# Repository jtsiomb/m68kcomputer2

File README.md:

Homebrew 32bit computer
=======================

About
-----
Following after my minimal 16bit 68010 computer design
(https://github.com/jtsiomb/m68kcomputer) this is an attempt to make a much
more advanced 32bit computer, based on the Motorola 68030 CPU.

The main objective of this project is to make a stand-alone computer, capable of
running a custom UNIX system with virtual memory. The 68030 processor was chosen
because it has an on-chip MMU.

The plan is to include the following on the main board:
 - Analog video output
 - PS/2 keyboard controller
 - ATA hard drive interface for fixed storage
 - SD card for removable storage
 - 68881 floating point co-processor
 - Dual RS232 serial port
 - Battery-backed RTC

Directory structure:
 - `hw` - hardware: kicad files and pdf schematics.

Design Progress
---------------

### Main board ###
 - [X] Schematic: almost completed, minor tweaks, video left for an expansion
 - [ ] PCB layout: not started
 - [ ] Firmware: not started
 - [ ] Boot ROM monitor: not started
 - [ ] Operating system: not started

### Video expansion card ###
 - [ ] Schematic
 - [ ] PCB layout
 - [ ] OS support

### Audio expansion card ###
 - [ ] Schematic
 - [ ] PCB layout
 - [ ] OS support

License
-------
Copyright (C) 2022 John Tsiombikas <nuclear@member.fsf.org>

You are free to use, reproduce, modify, and redistribute any part of this
project, provided you make any derivative work you release, freely available
under the same terms.

Both hardware designs, and software parts of this project, are released under
the terms of the GNU General Public License v3, or at your option any later
version published by the Free Software Foundation. See `LICENSE` for details.

To comply with the license, when releasing derivative hardware designs, you
must provide the full EDA project files, GAL equation files, and of course
firmware/software source code. Releasing only images of schematics, gerbers,
JED files, and firmware binaries is *not* sufficient for compliance.

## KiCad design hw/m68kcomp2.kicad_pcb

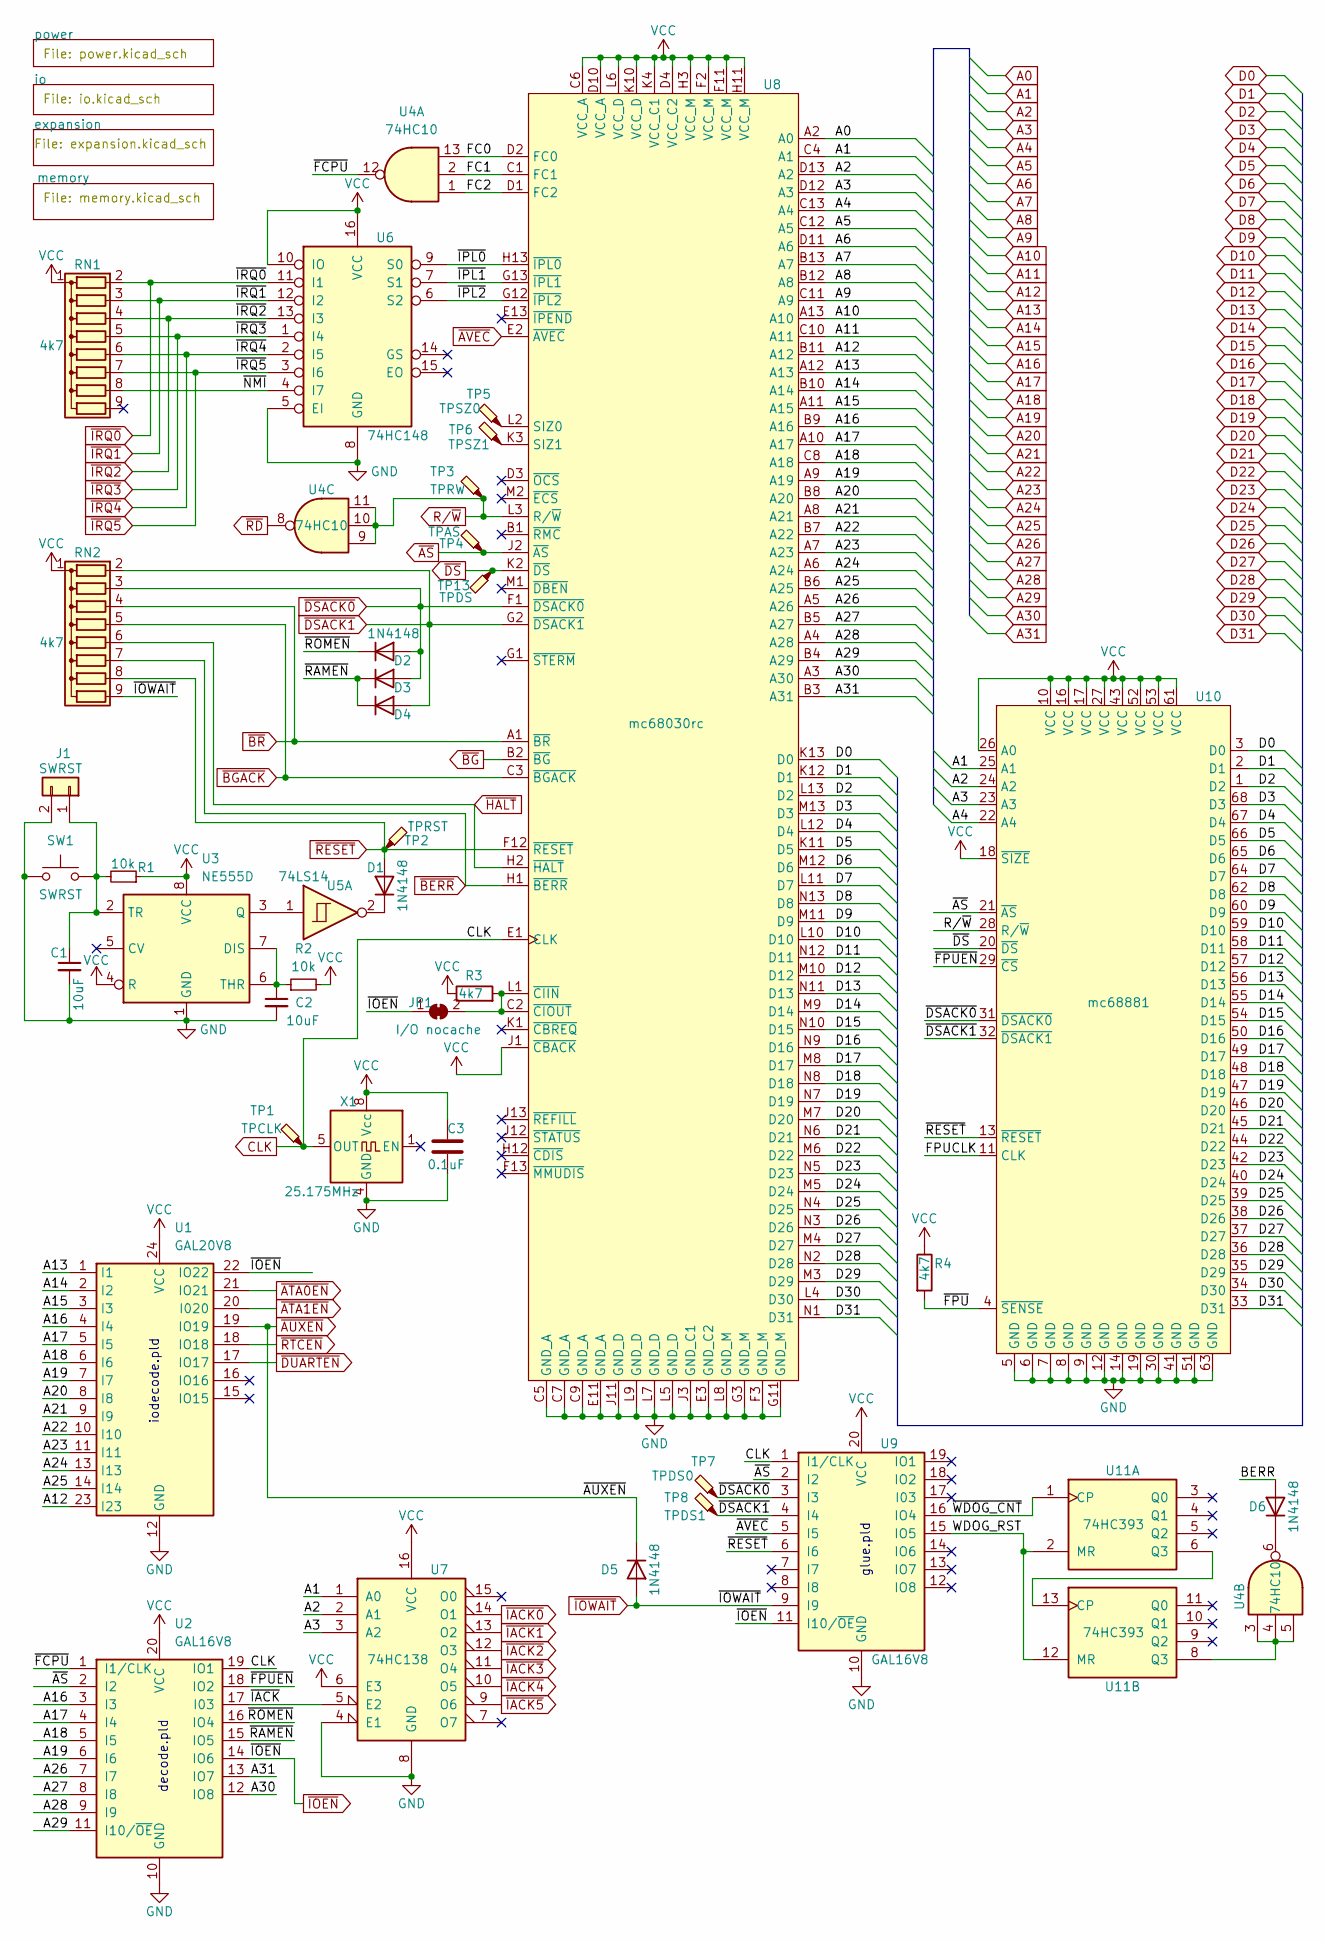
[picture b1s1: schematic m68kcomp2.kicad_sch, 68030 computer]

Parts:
C1, C2: 10uF; C_0805_2012Metric_Pad1.18x1.45mm_HandSolder
C3: 0.1uF; C_0805_2012Metric_Pad1.18x1.45mm_HandSolder
D1, D2, D3, D4, D5, D6: 1N4148; D_DO-35_SOD27_P7.62mm_Horizontal
J1: SWRST; PinHeader_1x02_P2.54mm_Vertical
JP1: I/O nocache; SolderJumper-2_P1.3mm_Bridged_RoundedPad1.0x1.5mm
R1, R2: 10k; R_0805_2012Metric_Pad1.20x1.40mm_HandSolder
R3, R4: 4k7; R_0805_2012Metric_Pad1.20x1.40mm_HandSolder
RN1, RN2: 4k7; R_Array_SIP9
SW1: SWRST; SW_SPST_EVPBF
TP1: TPCLK; TestPoint_Pad_D1.5mm
TP2: TPRST; TestPoint_Pad_D1.5mm
TP3: TPRW; TestPoint_Pad_D1.5mm
TP4: TPAS; TestPoint_Pad_D1.5mm
TP5: TPSZ0; TestPoint_Pad_D1.5mm
TP6: TPSZ1; TestPoint_Pad_D1.5mm
TP7: TPDS0; TestPoint_Pad_D1.5mm
TP8: TPDS1; TestPoint_Pad_D1.5mm
TP13: TPDS; TestPoint_Pad_D1.5mm
U1: GAL20V8; DIP-24_W7.62mm_Socket
U2, U9: GAL16V8; DIP-20_W7.62mm_Socket
U3: NE555D; SOIC-8_3.9x4.9mm_P1.27mm
U4: 74HC10; SO-14_3.9x8.65mm_P1.27mm
U5: 74LS14; SO-14_3.9x8.65mm_P1.27mm
U6: 74HC148; SO-16_3.9x9.9mm_P1.27mm
U7: 74HC138; SO-16_3.9x9.9mm_P1.27mm
U8: mc68030rc
U10: mc68881; PLCC-68_THT-Socket
U11: 74HC393; SO-14_3.9x8.65mm_P1.27mm
X1: 25.175MHz; Oscillator_DIP-8

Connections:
/BERR: D6.2 (A)
/FC0: U4.13, U8.D2 (FC0)
/FC1: U4.2, U8.C1 (FC1)
/FC2: U4.1, U8.D1 (FC2)
/FPUCLK: U10.11 (CLK)
/WDOG_RST: U9.15 (IO5), U11.2 (MR), U11.12 (MR)
/~FCPU: U2.1 (I1/CLK), U4.12
/~FPUEN: U2.18 (IO2), U10.29 (~CS)
/~FPU: R4.2, U10.4 (~SENSE)
/~IACK: U2.17 (I03), U7.5 (E2)
/~IPL0: U6.9 (S0), U8.H13 (~IPL0)
/~IPL1: U6.7 (S1), U8.G13 (~IPL1)
/~IPL2: U6.6 (S2), U8.G12 (~IPL2)
/~NMI: RN1.8 (R7), U6.4 (I7)
/~RAMEN: D3.1 (K), D4.1 (K), U2.15 (IO5)
/~ROMEN: D2.1 (K), U2.16 (IO4)
/~WDOG_CNT: U9.16 (IO4), U11.1 (CP)
A0: U8.A2 (A0); also elsewhere on the board
A1: U7.1 (A0), U8.C4 (A1), U10.25 (A1); also elsewhere on the board
A2: U7.2 (A1), U8.D13 (A2), U10.24 (A2); also elsewhere on the board
A3: U7.3 (A2), U8.D12 (A3), U10.23 (A3); also elsewhere on the board
A4: U8.C13 (A4), U10.22 (A4); also elsewhere on the board
A5: U8.C12 (A5); also elsewhere on the board
A6: U8.D11 (A6); also elsewhere on the board
A7: U8.B13 (A7); also elsewhere on the board
A8: U8.B12 (A8); also elsewhere on the board
A9: U8.C11 (A9); also elsewhere on the board
A10: U8.A13 (A10); also elsewhere on the board
A11: U8.C10 (A11); also elsewhere on the board
A12: U1.23 (I23), U8.B11 (A12); also elsewhere on the board
A13: U1.1 (I1), U8.A12 (A13); also elsewhere on the board
A14: U1.2 (I2), U8.B10 (A14); also elsewhere on the board
A15: U1.3 (I3), U8.A11 (A15); also elsewhere on the board
A16: U1.4 (I4), U2.3 (I3), U8.B9 (A16); also elsewhere on the board
A17: U1.5 (I5), U2.4 (I4), U8.A10 (A17); also elsewhere on the board
A18: U1.6 (I6), U2.5 (I5), U8.C8 (A18); also elsewhere on the board
A19: U1.7 (I7), U2.6 (I6), U8.A9 (A19); also elsewhere on the board
A20: U1.8 (I8), U8.B8 (A20); also elsewhere on the board
A21: U1.9 (I9), U8.A8 (A21); also elsewhere on the board
A22: U1.10 (I10), U8.B7 (A22); also elsewhere on the board
A23: U1.11 (I11), U8.A7 (A23); also elsewhere on the board
A24: U1.13 (I13), U8.A6 (A24); also elsewhere on the board
A25: U1.14 (I14), U8.B6 (A25); also elsewhere on the board
A26: U2.7 (I7), U8.A5 (A26); also elsewhere on the board
A27: U2.8 (I8), U8.B5 (A27); also elsewhere on the board
A28: U2.9 (I9), U8.A4 (A28); also elsewhere on the board
A29: U2.11 (I10/~OE), U8.B4 (A29); also elsewhere on the board
A30: U2.12 (IO8), U8.A3 (A30); also elsewhere on the board
A31: U2.13 (IO7), U8.B3 (A31); also elsewhere on the board
CLK: TP1.1, U2.19 (IO1), U8.E1 (CLK), U9.1 (I1/CLK), X1.5 (OUT); also elsewhere on the board
D0: U8.K13 (D0), U10.3 (D0); also elsewhere on the board
D1: U8.K12 (D1), U10.2 (D1); also elsewhere on the board
D2: U8.L13 (D2), U10.1 (D2); also elsewhere on the board
D3: U8.M13 (D3), U10.68 (D3); also elsewhere on the board
D4: U8.L12 (D4), U10.67 (D4); also elsewhere on the board
D5: U8.K11 (D5), U10.66 (D5); also elsewhere on the board
D6: U8.M12 (D6), U10.65 (D6); also elsewhere on the board
D7: U8.L11 (D7), U10.64 (D7); also elsewhere on the board
D8: U8.N13 (D8), U10.62 (D8); also elsewhere on the board
D9: U8.M11 (D9), U10.60 (D9); also elsewhere on the board
D10: U8.L10 (D10), U10.59 (D10); also elsewhere on the board
D11: U8.N12 (D11), U10.58 (D11); also elsewhere on the board
D12: U8.M10 (D12), U10.57 (D12); also elsewhere on the board
D13: U8.N11 (D13), U10.56 (D13); also elsewhere on the board
D14: U8.M9 (D14), U10.55 (D14); also elsewhere on the board
D15: U8.N10 (D15), U10.54 (D15); also elsewhere on the board
D16: U8.N9 (D16), U10.50 (D16); also elsewhere on the board
D17: U8.M8 (D17), U10.49 (D17); also elsewhere on the board
D18: U8.N8 (D18), U10.48 (D18); also elsewhere on the board
D19: U8.N7 (D19), U10.47 (D19); also elsewhere on the board
D20: U8.M7 (D20), U10.46 (D20); also elsewhere on the board
D21: U8.N6 (D21), U10.45 (D21); also elsewhere on the board
D22: U8.M6 (D22), U10.44 (D22); also elsewhere on the board
D23: U8.N5 (D23), U10.42 (D23); also elsewhere on the board
D24: U8.M5 (D24), U10.40 (D24); also elsewhere on the board
D25: U8.N4 (D25), U10.39 (D25); also elsewhere on the board
D26: U8.N3 (D26), U10.38 (D26); also elsewhere on the board
D27: U8.M4 (D27), U10.37 (D27); also elsewhere on the board
D28: U8.N2 (D28), U10.36 (D28); also elsewhere on the board
D29: U8.M3 (D29), U10.35 (D29); also elsewhere on the board
D30: U8.L4 (D30), U10.34 (D30); also elsewhere on the board
D31: U8.N1 (D31), U10.33 (D31); also elsewhere on the board
GND: C1.2, C2.2, C3.2, J1.2, SW1.1, U1.12 (GND), U2.10 (GND), U3.1 (GND), U6.5 (EI), U6.8 (GND), U7.4 (E1), U7.8 (GND), U8.C5 (GND_A), U8.C7 (GND_A), U8.C9 (GND_A), U8.E3 (GND_C2), U8.E11 (GND_A), U8.F3 (GND_M), U8.G3 (GND_M), U8.G11 (GND_M), U8.J3 (GND_C1), U8.J11 (GND_D), U8.L5 (GND_D), U8.L7 (GND_D), U8.L8 (GND_M), U8.L9 (GND_D), U9.10 (GND), U10.5 (GND), U10.6 (GND), U10.7 (GND), U10.8 (GND), U10.9 (GND), U10.12 (GND), U10.14 (GND), U10.19 (GND), U10.30 (GND), U10.41 (GND), U10.51 (GND), U10.63 (GND), X1.4 (GND); also elsewhere on the board
unnamed: C1.1, J1.1, R1.2, SW1.2, U3.2 (TR)
unnamed: C2.1, R2.1, U3.6 (THR), U3.7 (DIS)
unnamed: D1.1 (K), U5.2
unnamed: D6.1 (K), U4.6
unnamed: JP1.2 (B), R3.2, U8.C2 (~CIOUT), U8.L1 (~CIIN)
unnamed: TP5.1, U8.L2 (SIZ0)
unnamed: TP6.1, U8.K3 (SIZ1)
unnamed: U3.3 (Q), U5.1
unnamed: U4.3, U4.4, U4.5, U11.8 (Q3)
unnamed: U11.6 (Q3), U11.13 (CP)
R/~W: TP3.1, U4.9, U4.10, U4.11, U8.L3 (R/~W), U10.28 (R/~W); also elsewhere on the board
VCC: C3.1, R1.1, R2.2, R3.1, R4.1, RN1.1 (common), RN2.1 (common), U1.24 (VCC), U2.20 (VCC), U3.4 (R), U3.8 (VCC), U6.10 (IO), U6.16 (VCC), U7.6 (E3), U7.16 (VCC), U8.C6 (VCC_A), U8.D4 (VCC_C2), U8.D10 (VCC_A), U8.F2 (VCC_M), U8.F11 (VCC_M), U8.H3 (VCC_M), U8.H11 (VCC_M), U8.J1 (~CBACK), U8.K4 (VCC_C1), U8.K10 (VCC_D), U8.L6 (VCC_D), U9.20 (VCC), U10.10 (VCC), U10.16 (VCC), U10.17 (VCC), U10.18 (~SIZE), U10.26 (A0), U10.27 (VCC), U10.43 (VCC), U10.52 (VCC), U10.53 (VCC), U10.61 (VCC), X1.8 (Vcc); also elsewhere on the board
~AS: TP4.1, U2.2 (I2), U8.J2 (~AS), U9.2 (I2), U10.21 (~AS); also elsewhere on the board
~ATA0EN: U1.21 (IO21); also elsewhere on the board
~ATA1EN: U1.20 (I020); also elsewhere on the board
~AUXEN: D5.1 (K), U1.19 (IO19); also elsewhere on the board
~AVEC: U8.E2 (~AVEC), U9.5 (I5); also elsewhere on the board
~BERR: RN2.7 (R6), U8.H1 (~BERR); also elsewhere on the board
~BGACK: RN2.5 (R4), U8.C3 (~BGACK); also elsewhere on the board
~BG: U8.B2 (~BG); also elsewhere on the board
~BR: RN2.4 (R3), U8.A1 (~BR); also elsewhere on the board
~DSACK0: D2.2 (A), D3.2 (A), RN2.3 (R2), TP7.1, U8.F1 (~DSACK0), U9.3 (I3), U10.31 (~DSACK0); also elsewhere on the board
~DSACK1: D4.2 (A), RN2.2 (R1), TP8.1, U8.G2 (~DSACK1), U9.4 (I4), U10.32 (~DSACK1); also elsewhere on the board
~DS: TP13.1, U8.K2 (~DS), U10.20 (~DS); also elsewhere on the board
~DUARTEN: U1.17 (IO17); also elsewhere on the board
~HALT: RN2.6 (R5), U8.H2 (~HALT); also elsewhere on the board
~IACK0: U7.14 (O1); also elsewhere on the board
~IACK1: U7.13 (O2); also elsewhere on the board
~IACK2: U7.12 (O3); also elsewhere on the board
~IACK3: U7.11 (O4); also elsewhere on the board
~IACK4: U7.10 (O5); also elsewhere on the board
~IACK5: U7.9 (O6); also elsewhere on the board
~IOEN: JP1.1 (A), U1.22 (IO22), U2.14 (IO6), U9.11 (I10/~OE); also elsewhere on the board
~IOWAIT: D5.2 (A), RN2.9 (R8), U9.9 (I9); also elsewhere on the board
~IRQ0: RN1.2 (R1), U6.11 (I1); also elsewhere on the board
~IRQ1: RN1.3 (R2), U6.12 (I2); also elsewhere on the board
~IRQ2: RN1.4 (R3), U6.13 (I3); also elsewhere on the board
~IRQ3: RN1.5 (R4), U6.1 (I4); also elsewhere on the board
~IRQ4: RN1.6 (R5), U6.2 (I5); also elsewhere on the board
~IRQ5: RN1.7 (R6), U6.3 (I6); also elsewhere on the board
~RD: U4.8; also elsewhere on the board
~RESET: D1.2 (A), RN2.8 (R7), TP2.1, U8.F12 (~RESET), U9.6 (I6), U10.13 (~RESET); also elsewhere on the board
~RTCEN: U1.18 (IO18); also elsewhere on the board

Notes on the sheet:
iodecode.pld
decode.pld
glue.pld

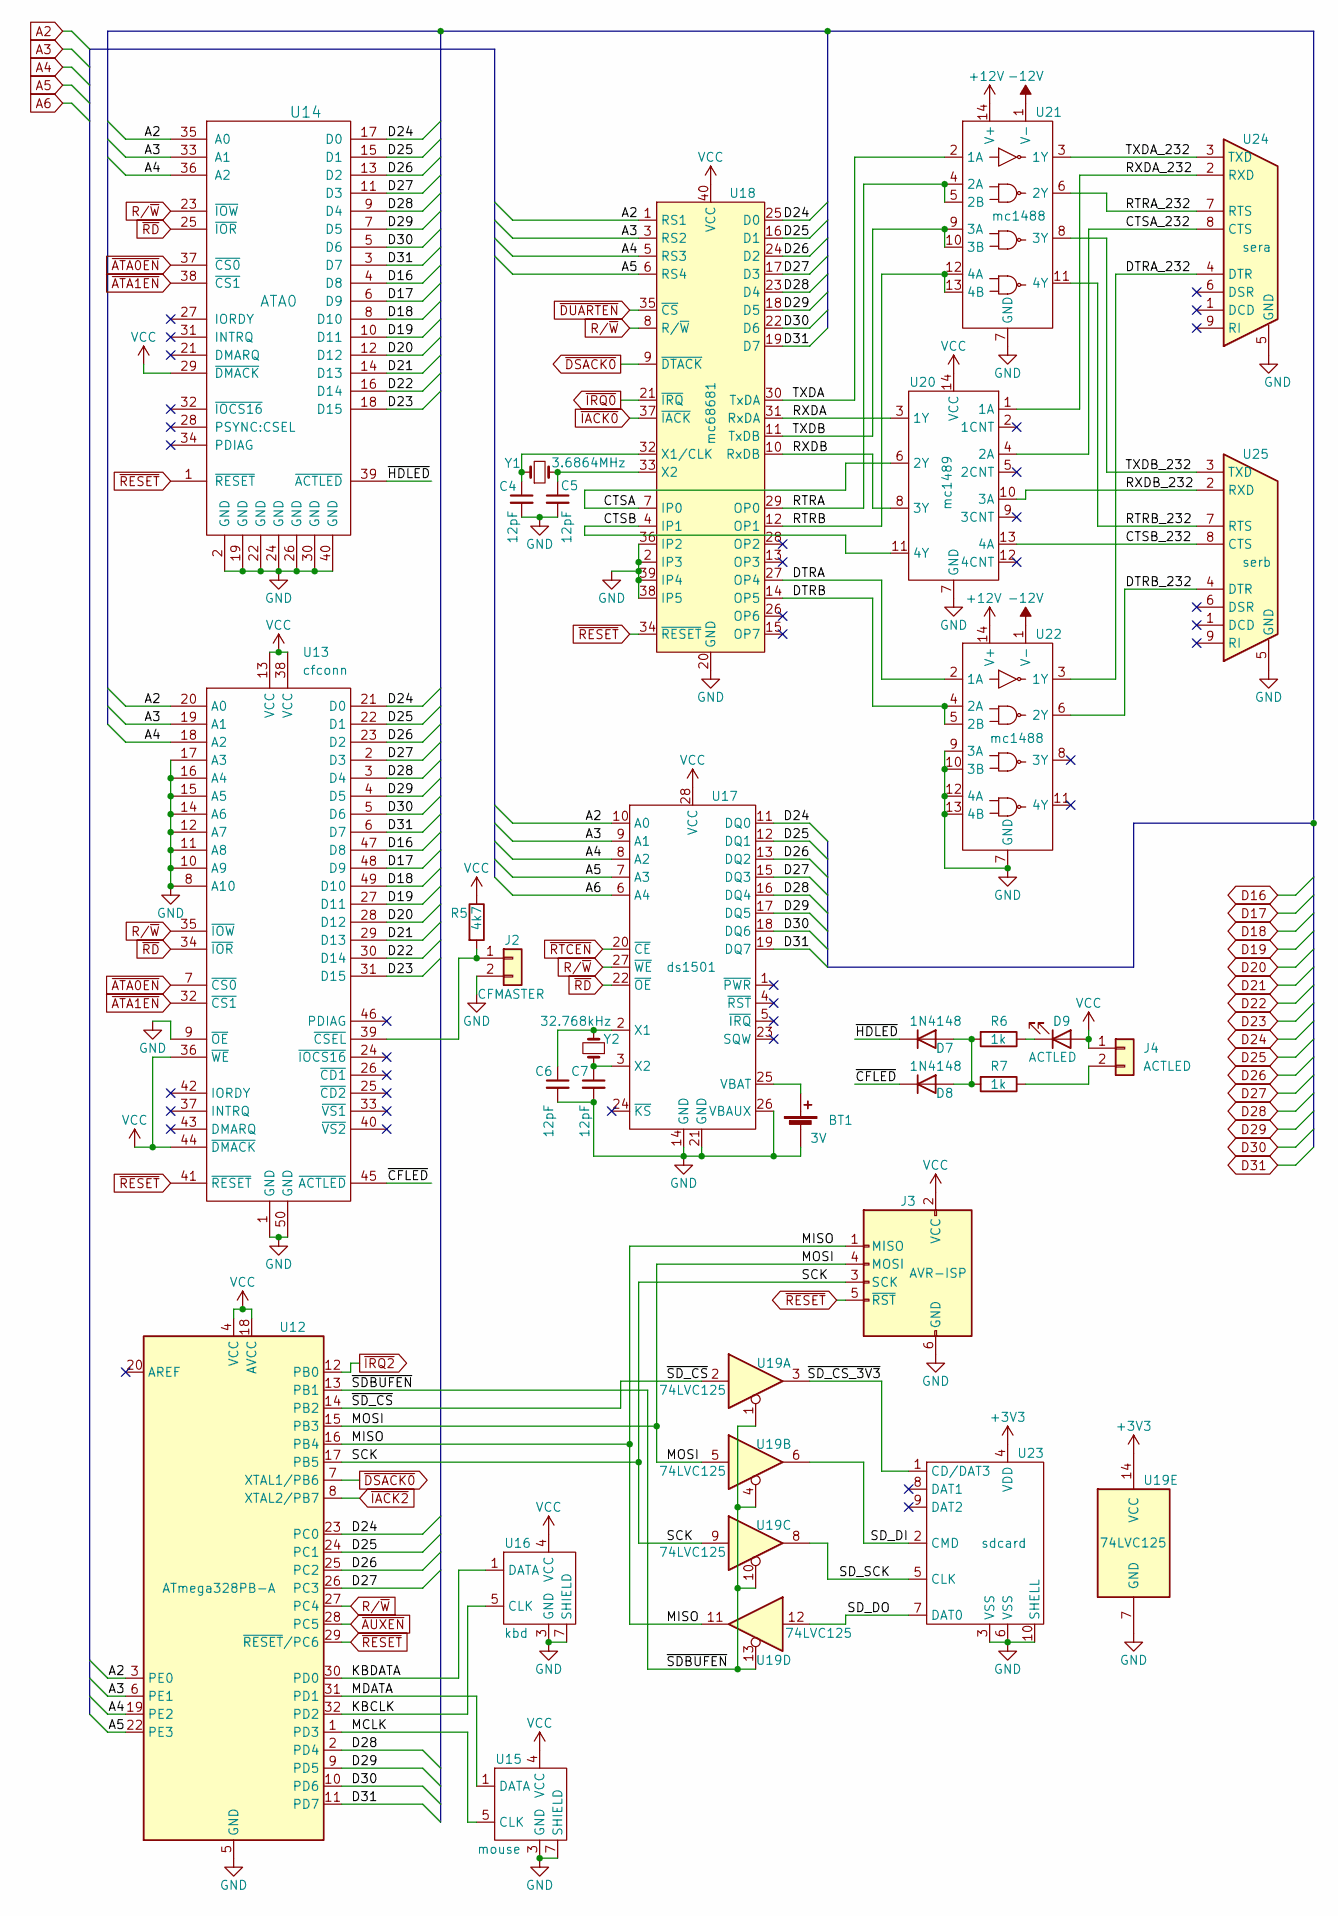
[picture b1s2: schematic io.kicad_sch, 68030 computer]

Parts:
BT1: 3V; BatteryHolder_Keystone_1060_1x2032
C4, C5, C6, C7: 12pF; C_0805_2012Metric_Pad1.18x1.45mm_HandSolder
D7, D8: 1N4148; D_DO-35_SOD27_P7.62mm_Horizontal
D9: ACTLED; LED_0805_2012Metric_Pad1.15x1.40mm_HandSolder
J2: CFMASTER; PinHeader_1x02_P2.54mm_Vertical
J3: AVR-ISP; IDC-Header_2x03_P2.54mm_Vertical
J4: ACTLED; PinHeader_1x02_P2.54mm_Vertical
R5: 4k7; R_0805_2012Metric_Pad1.20x1.40mm_HandSolder
R6, R7: 1k; R_0805_2012Metric_Pad1.20x1.40mm_HandSolder
U12: ATmega328PB-A; TQFP-32_7x7mm_P0.8mm
U13: cfconn; CF-Card_3M_N7E50-7516PK-20-WF
U14: ATA0; IDC-Header_2x20_P2.54mm_Vertical
U15: mouse; minidin6
U16: kbd; minidin6
U17: ds1501; SOIC-28W_7.5x17.9mm_P1.27mm
U18: mc68681; DIP-40_W15.24mm_Socket
U19: 74LVC125; SO-14_3.9x8.65mm_P1.27mm
U20: mc1489; SO-14_3.9x8.65mm_P1.27mm
U21, U22: mc1488; SO-14_3.9x8.65mm_P1.27mm
U23: sdcard; SD_TE_2041021
U24: sera; DSUB-9_Male_Horizontal_P2.77x2.84mm_EdgePinOffset7.70mm_Hou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
U25: serb; DSUB-9_Male_Horizontal_P2.77x2.84mm_EdgePinOffset7.70mm_Hou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
Y1: 3.6864MHz; Crystal_SMD_ECS_CSM3X-2Pin_7.6x4.1mm
Y2: 32.768kHz; Crystal_SMD_ECS_CSM3X-2Pin_7.6x4.1mm

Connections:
+3V3: U19.14 (VCC), U23.4 (VDD); also elsewhere on the board
+12V: U21.14 (V+), U22.14 (V+); also elsewhere on the board
-12V: U21.1 (V-), U22.1 (V-); also elsewhere on the board
/io/CTSA: U18.7 (IP0), U20.6 (2Y)
/io/CTSA_232: U20.4 (2A), U24.8 (CTS)
/io/CTSB: U18.4 (IP1), U20.11 (4Y)
/io/CTSB_232: U20.13 (4A), U25.8 (CTS)
/io/DTRA: U18.27 (OP4), U22.2 (1A)
/io/DTRA_232: U22.3 (1Y), U24.4 (DTR)
/io/DTRB: U18.14 (OP5), U22.4 (2A), U22.5 (2B)
/io/DTRB_232: U22.6 (2Y), U25.4 (DTR)
/io/KBCLK: U12.32 (PD2), U16.5 (CLK)
/io/KBDATA: U12.30 (PD0), U16.1 (DATA)
/io/MCLK: U12.1 (PD3), U15.5 (CLK)
/io/MDATA: U12.31 (PD1), U15.1 (DATA)
/io/MISO: J3.1 (MISO), U12.16 (PB4), U19.11
/io/MOSI: J3.4 (MOSI), U12.15 (PB3), U19.5
/io/RTRA: U18.29 (OP0), U21.4 (2A), U21.5 (2B)
/io/RTRA_232: U21.6 (2Y), U24.7 (RTS)
/io/RTRB: U18.12 (OP1), U21.12 (4A), U21.13 (4B)
/io/RTRB_232: U21.11 (4Y), U25.7 (RTS)
/io/RXDA: U18.31 (RxDA), U20.3 (1Y)
/io/RXDA_232: U20.1 (1A), U24.2 (RXD)
/io/RXDB: U18.10 (RxDB), U20.8 (3Y)
/io/RXDB_232: U20.10 (3A), U25.2 (RXD)
/io/SCK: J3.3 (SCK), U12.17 (PB5), U19.9
/io/SD_DI: U19.6, U23.2 (CMD)
/io/SD_DO: U19.12, U23.7 (DAT0)
/io/SD_SCK: U19.8, U23.5 (CLK)
/io/TXDA: U18.30 (TxDA), U21.2 (1A)
/io/TXDA_232: U21.3 (1Y), U24.3 (TXD)
/io/TXDB: U18.11 (TxDB), U21.9 (3A), U21.10 (3B)
/io/TXDB_232: U21.8 (3Y), U25.3 (TXD)
/io/~CFLED: D8.1 (K), U13.45 (~ACTLED)
/io/~HDLED: D7.1 (K), U14.39 (~ACTLED)
/io/~SDBUFEN: U12.13 (PB1), U19.1, U19.4, U19.10, U19.13
/io/~SD_CS_3V3: U19.3, U23.1 (CD/DAT3)
/io/~SD_CS: U12.14 (PB2), U19.2
A2: U12.3 (PE0), U13.20 (A0), U14.35 (A0), U17.10 (A0), U18.1 (RS1); also elsewhere on the board
A3: U12.6 (PE1), U13.19 (A1), U14.33 (A1), U17.9 (A1), U18.3 (RS2); also elsewhere on the board
A4: U12.19 (PE2), U13.18 (A2), U14.36 (A2), U17.8 (A2), U18.5 (RS3); also elsewhere on the board
A5: U12.22 (PE3), U17.7 (A3), U18.6 (RS4); also elsewhere on the board
A6: U17.6 (A4); also elsewhere on the board
D16: U13.47 (D8), U14.4 (D8); also elsewhere on the board
D17: U13.48 (D9), U14.6 (D9); also elsewhere on the board
D18: U13.49 (D10), U14.8 (D10); also elsewhere on the board
D19: U13.27 (D11), U14.10 (D11); also elsewhere on the board
D20: U13.28 (D12), U14.12 (D12); also elsewhere on the board
D21: U13.29 (D13), U14.14 (D13); also elsewhere on the board
D22: U13.30 (D14), U14.16 (D14); also elsewhere on the board
D23: U13.31 (D15), U14.18 (D15); also elsewhere on the board
D24: U12.23 (PC0), U13.21 (D0), U14.17 (D0), U17.11 (DQ0), U18.25 (D0); also elsewhere on the board
D25: U12.24 (PC1), U13.22 (D1), U14.15 (D1), U17.12 (DQ1), U18.16 (D1); also elsewhere on the board
D26: U12.25 (PC2), U13.23 (D2), U14.13 (D2), U17.13 (DQ2), U18.24 (D2); also elsewhere on the board
D27: U12.26 (PC3), U13.2 (D3), U14.11 (D3), U17.15 (DQ3), U18.17 (D3); also elsewhere on the board
D28: U12.2 (PD4), U13.3 (D4), U14.9 (D4), U17.16 (DQ4), U18.23 (D4); also elsewhere on the board
D29: U12.9 (PD5), U13.4 (D5), U14.7 (D5), U17.17 (DQ5), U18.18 (D5); also elsewhere on the board
D30: U12.10 (PD6), U13.5 (D6), U14.5 (D6), U17.18 (DQ6), U18.22 (D6); also elsewhere on the board
D31: U12.11 (PD7), U13.6 (D7), U14.3 (D7), U17.19 (DQ7), U18.19 (D7); also elsewhere on the board
GND: BT1.2 (-), C4.2, C5.2, C6.2, C7.2, J2.2, J3.6 (GND), U12.5 (GND), U12.21 (GND), U13.1 (GND), U13.8 (A10), U13.9 (~OE), U13.10 (A9), U13.11 (A8), U13.12 (A7), U13.14 (A6), U13.15 (A5), U13.16 (A4), U13.17 (A3), U13.50 (GND), U14.2 (GND), U14.19 (GND), U14.22 (GND), U14.24 (GND), U14.26 (GND), U14.30 (GND), U14.40 (GND), U15.3 (GND), U15.7 (SHIELD), U16.3 (GND), U16.7 (SHIELD), U17.14 (GND), U17.21 (GND), U17.26 (VBAUX), U18.2 (IP3), U18.20 (GND), U18.36 (IP2), U18.38 (IP5), U18.39 (IP4), U19.7 (GND), U20.7 (GND), U21.7 (GND), U22.7 (GND), U22.9 (3A), U22.10 (3B), U22.12 (4A), U22.13 (4B), U23.3 (VSS), U23.6 (VSS), U23.10 (SHELL), U24.5 (GND), U25.5 (GND); also elsewhere on the board
unnamed: BT1.1 (+), U17.25 (VBAT)
unnamed: C4.1, U18.32 (X1/CLK), Y1.1
unnamed: C5.1, U18.33 (X2), Y1.2
unnamed: C6.1, U17.2 (X1), Y2.2
unnamed: C7.1, U17.3 (X2), Y2.1
unnamed: D7.2 (A), D8.2 (A), R6.2, R7.2
unnamed: D9.1 (K), R6.1
unnamed: J2.1, R5.2, U13.39 (~CSEL)
unnamed: J4.2, R7.1
R/~W: U12.27 (PC4), U13.35 (~IOW), U14.23 (~IOW), U17.27 (~WE), U18.8 (R/~W); also elsewhere on the board
VCC: D9.2 (A), J3.2 (VCC), J4.1, R5.1, U12.4 (VCC), U12.18 (AVCC), U13.13 (VCC), U13.36 (~WE), U13.38 (VCC), U13.44 (~DMACK), U14.29 (~DMACK), U15.4 (VCC), U16.4 (VCC), U17.28 (VCC), U18.40 (VCC), U20.14 (VCC); also elsewhere on the board
~ATA0EN: U13.7 (~CS0), U14.37 (~CS0); also elsewhere on the board
~ATA1EN: U13.32 (~CS1), U14.38 (~CS1); also elsewhere on the board
~AUXEN: U12.28 (PC5); also elsewhere on the board
~DSACK0: U12.7 (XTAL1/PB6), U18.9 (~DTACK); also elsewhere on the board
~DUARTEN: U18.35 (~CS); also elsewhere on the board
~IACK0: U18.37 (~IACK); also elsewhere on the board
~IACK2: U12.8 (XTAL2/PB7); also elsewhere on the board
~IRQ0: U18.21 (~IRQ); also elsewhere on the board
~IRQ2: U12.12 (PB0); also elsewhere on the board
~RD: U13.34 (~IOR), U14.25 (~IOR), U17.22 (~OE); also elsewhere on the board
~RESET: J3.5 (~RST), U12.29 (~RESET/PC6), U13.41 (~RESET), U14.1 (~RESET), U18.34 (~RESET); also elsewhere on the board
~RTCEN: U17.20 (~CE); also elsewhere on the board

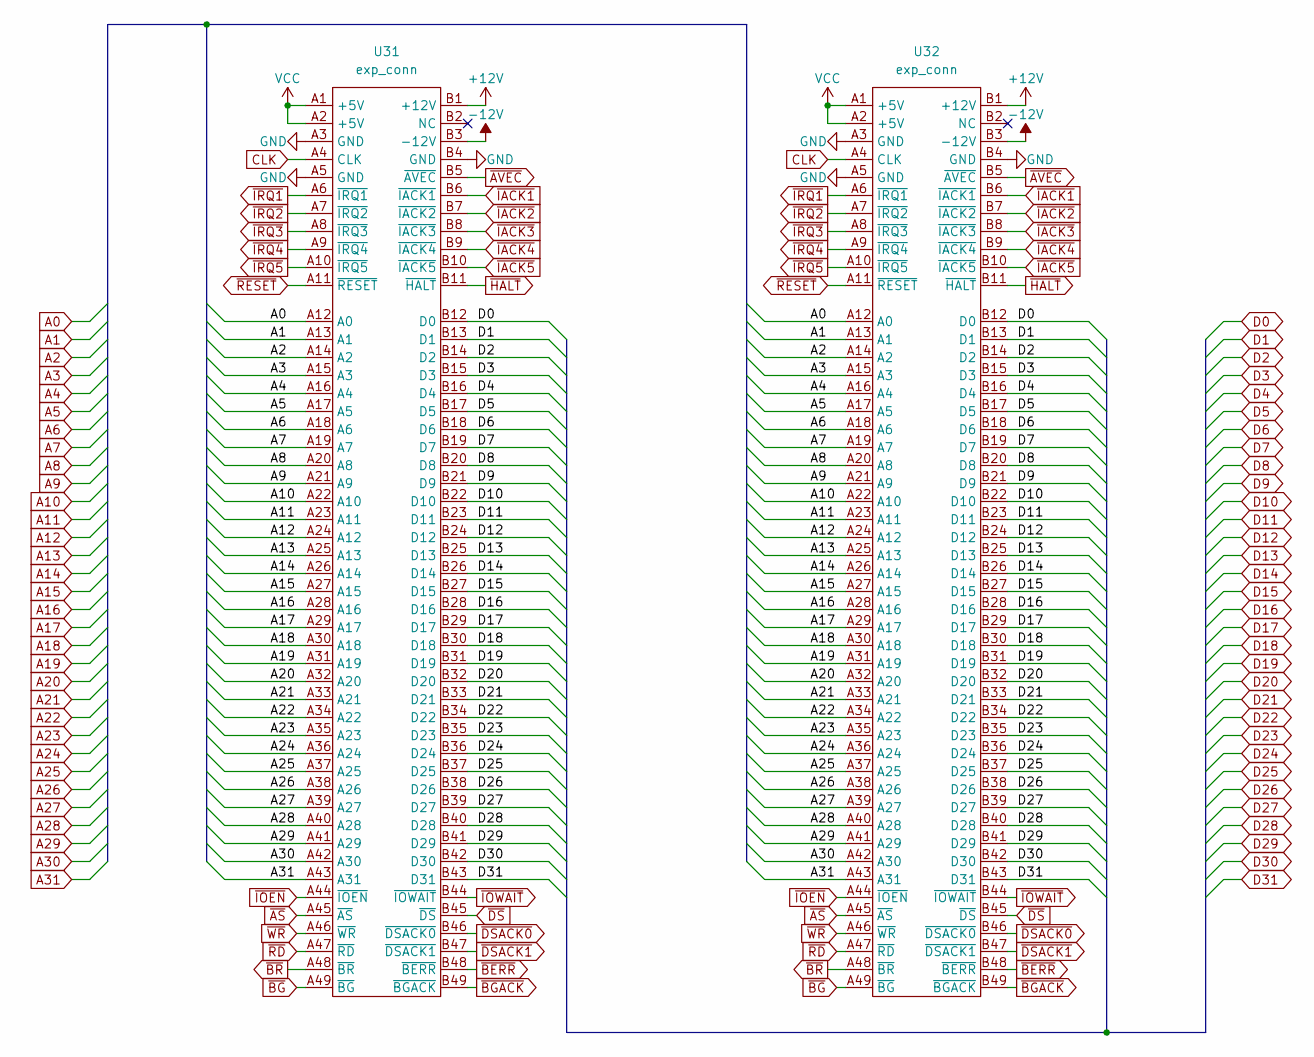
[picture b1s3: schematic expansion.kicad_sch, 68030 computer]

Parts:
U31, U32: exp_conn; pcix8slot

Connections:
+12V: U31.B1 (+12V), U32.B1 (+12V); also elsewhere on the board
-12V: U31.B3 (-12V), U32.B3 (-12V); also elsewhere on the board
A0: U31.A12 (A0), U32.A12 (A0); also elsewhere on the board
A1: U31.A13 (A1), U32.A13 (A1); also elsewhere on the board
A2: U31.A14 (A2), U32.A14 (A2); also elsewhere on the board
A3: U31.A15 (A3), U32.A15 (A3); also elsewhere on the board
A4: U31.A16 (A4), U32.A16 (A4); also elsewhere on the board
A5: U31.A17 (A5), U32.A17 (A5); also elsewhere on the board
A6: U31.A18 (A6), U32.A18 (A6); also elsewhere on the board
A7: U31.A19 (A7), U32.A19 (A7); also elsewhere on the board
A8: U31.A20 (A8), U32.A20 (A8); also elsewhere on the board
A9: U31.A21 (A9), U32.A21 (A9); also elsewhere on the board
A10: U31.A22 (A10), U32.A22 (A10); also elsewhere on the board
A11: U31.A23 (A11), U32.A23 (A11); also elsewhere on the board
A12: U31.A24 (A12), U32.A24 (A12); also elsewhere on the board
A13: U31.A25 (A13), U32.A25 (A13); also elsewhere on the board
A14: U31.A26 (A14), U32.A26 (A14); also elsewhere on the board
A15: U31.A27 (A15), U32.A27 (A15); also elsewhere on the board
A16: U31.A28 (A16), U32.A28 (A16); also elsewhere on the board
A17: U31.A29 (A17), U32.A29 (A17); also elsewhere on the board
A18: U31.A30 (A18), U32.A30 (A18); also elsewhere on the board
A19: U31.A31 (A19), U32.A31 (A19); also elsewhere on the board
A20: U31.A32 (A20), U32.A32 (A20); also elsewhere on the board
A21: U31.A33 (A21), U32.A33 (A21); also elsewhere on the board
A22: U31.A34 (A22), U32.A34 (A22); also elsewhere on the board
A23: U31.A35 (A23), U32.A35 (A23); also elsewhere on the board
A24: U31.A36 (A24), U32.A36 (A24); also elsewhere on the board
A25: U31.A37 (A25), U32.A37 (A25); also elsewhere on the board
A26: U31.A38 (A26), U32.A38 (A26); also elsewhere on the board
A27: U31.A39 (A27), U32.A39 (A27); also elsewhere on the board
A28: U31.A40 (A28), U32.A40 (A28); also elsewhere on the board
A29: U31.A41 (A29), U32.A41 (A29); also elsewhere on the board
A30: U31.A42 (A30), U32.A42 (A30); also elsewhere on the board
A31: U31.A43 (A31), U32.A43 (A31); also elsewhere on the board
CLK: U31.A4 (CLK), U32.A4 (CLK); also elsewhere on the board
D0: U31.B12 (D0), U32.B12 (D0); also elsewhere on the board
D1: U31.B13 (D1), U32.B13 (D1); also elsewhere on the board
D2: U31.B14 (D2), U32.B14 (D2); also elsewhere on the board
D3: U31.B15 (D3), U32.B15 (D3); also elsewhere on the board
D4: U31.B16 (D4), U32.B16 (D4); also elsewhere on the board
D5: U31.B17 (D5), U32.B17 (D5); also elsewhere on the board
D6: U31.B18 (D6), U32.B18 (D6); also elsewhere on the board
D7: U31.B19 (D7), U32.B19 (D7); also elsewhere on the board
D8: U31.B20 (D8), U32.B20 (D8); also elsewhere on the board
D9: U31.B21 (D9), U32.B21 (D9); also elsewhere on the board
D10: U31.B22 (D10), U32.B22 (D10); also elsewhere on the board
D11: U31.B23 (D11), U32.B23 (D11); also elsewhere on the board
D12: U31.B24 (D12), U32.B24 (D12); also elsewhere on the board
D13: U31.B25 (D13), U32.B25 (D13); also elsewhere on the board
D14: U31.B26 (D14), U32.B26 (D14); also elsewhere on the board
D15: U31.B27 (D15), U32.B27 (D15); also elsewhere on the board
D16: U31.B28 (D16), U32.B28 (D16); also elsewhere on the board
D17: U31.B29 (D17), U32.B29 (D17); also elsewhere on the board
D18: U31.B30 (D18), U32.B30 (D18); also elsewhere on the board
D19: U31.B31 (D19), U32.B31 (D19); also elsewhere on the board
D20: U31.B32 (D20), U32.B32 (D20); also elsewhere on the board
D21: U31.B33 (D21), U32.B33 (D21); also elsewhere on the board
D22: U31.B34 (D22), U32.B34 (D22); also elsewhere on the board
D23: U31.B35 (D23), U32.B35 (D23); also elsewhere on the board
D24: U31.B36 (D24), U32.B36 (D24); also elsewhere on the board
D25: U31.B37 (D25), U32.B37 (D25); also elsewhere on the board
D26: U31.B38 (D26), U32.B38 (D26); also elsewhere on the board
D27: U31.B39 (D27), U32.B39 (D27); also elsewhere on the board
D28: U31.B40 (D28), U32.B40 (D28); also elsewhere on the board
D29: U31.B41 (D29), U32.B41 (D29); also elsewhere on the board
D30: U31.B42 (D30), U32.B42 (D30); also elsewhere on the board
D31: U31.B43 (D31), U32.B43 (D31); also elsewhere on the board
GND: U31.A3 (GND), U31.A5 (GND), U31.B4 (GND), U32.A3 (GND), U32.A5 (GND), U32.B4 (GND); also elsewhere on the board
VCC: U31.A1 (+5V), U31.A2 (+5V), U32.A1 (+5V), U32.A2 (+5V); also elsewhere on the board
~AS: U31.A45 (~AS), U32.A45 (~AS); also elsewhere on the board
~AVEC: U31.B5 (~AVEC), U32.B5 (~AVEC); also elsewhere on the board
~BERR: U31.B48 (~BERR), U32.B48 (~BERR); also elsewhere on the board
~BGACK: U31.B49 (~BGACK), U32.B49 (~BGACK); also elsewhere on the board
~BG: U31.A49 (~BG), U32.A49 (~BG); also elsewhere on the board
~BR: U31.A48 (~BR), U32.A48 (~BR); also elsewhere on the board
~DSACK0: U31.B46 (~DSACK0), U32.B46 (~DSACK0); also elsewhere on the board
~DSACK1: U31.B47 (~DSACK1), U32.B47 (~DSACK1); also elsewhere on the board
~DS: U31.B45 (~DS), U32.B45 (~DS); also elsewhere on the board
~HALT: U31.B11 (~HALT), U32.B11 (~HALT); also elsewhere on the board
~IACK1: U31.B6 (~IACK1), U32.B6 (~IACK1); also elsewhere on the board
~IACK2: U31.B7 (~IACK2), U32.B7 (~IACK2); also elsewhere on the board
~IACK3: U31.B8 (~IACK3), U32.B8 (~IACK3); also elsewhere on the board
~IACK4: U31.B9 (~IACK4), U32.B9 (~IACK4); also elsewhere on the board
~IACK5: U31.B10 (~IACK5), U32.B10 (~IACK5); also elsewhere on the board
~IOEN: U31.A44 (~IOEN), U32.A44 (~IOEN); also elsewhere on the board
~IOWAIT: U31.B44 (~IOWAIT), U32.B44 (~IOWAIT); also elsewhere on the board
~IRQ1: U31.A6 (~IRQ1), U32.A6 (~IRQ1); also elsewhere on the board
~IRQ2: U31.A7 (~IRQ2), U32.A7 (~IRQ2); also elsewhere on the board
~IRQ3: U31.A8 (~IRQ3), U32.A8 (~IRQ3); also elsewhere on the board
~IRQ4: U31.A9 (~IRQ4), U32.A9 (~IRQ4); also elsewhere on the board
~IRQ5: U31.A10 (~IRQ5), U32.A10 (~IRQ5); also elsewhere on the board
~RD: U31.A47 (~RD), U32.A47 (~RD); also elsewhere on the board
~RESET: U31.A11 (~RESET), U32.A11 (~RESET); also elsewhere on the board
~WR: U31.A46 (~WR), U32.A46 (~WR)

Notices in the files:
hw/expansion.kicad_sch:
Free hardware design - GNU General Public License v3
